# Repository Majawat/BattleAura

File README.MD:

# BattleAura

### LEDs & Sound for Warhammer

Just a fun project to add sound and lights to my Warhammer tanks. ESP32 + DFPlayer Mini + LEDs.

## What I Did

- MP3 sounds (engine, guns, etc.) from SD card
- Neopixel LEDs for glowy bits
- ESP32 does the brains, DFPlayer does the noise
- I just use buttons for triggers, but you could do more

## Parts I Used

- Seeed Studio Xaio ESP32-C3 dev board
- DFPlayer Mini
- microSD card (with MP3s)
- LEDs
- Speaker (8Ω)

## Wiring

ESP32 TX -> DFPlayer RX
ESP32 RX -> DFPlayer TX
GNDs together
5V to DFPlayer
Speaker to DFPlayer

### LED Pin assignment

- D0: Candle Fibers 1 - 3mm warm white, 3v
- D1: Candle Fibers 2 - 3mm warm white, 3v
- D2: Brazier - Chip (3.2mm) warm white, 3v
- D3: Console screen - WS2812B RGB, 5v
- D4: Weapon 1 - Nano (1.6mm) warm white, 3v
- D5: Weapon 2 - Nano (1.6mm) warm white, 3v
- D8: Engine stack 1 - Chip (3.2mm) warm white, 3v
- D9: Engine stack 2 - Chip (3.2mm) warm white, 3v
- D10: ?

### Audio files assignments
 - 0002 - Tank engine idle
 - 0003 - Weapon 1 fire
 - 0004 - Weapon 2 fire
 - 0005 - Taking hits
 - 0006 - Engine revving
 - 0007 - Destroyed
 - 0008 - Limited big weapon
 - 0009 - Killed another unit

 #### Audacity settings
  - Track > Mix > Mix stero down to Mono
  - Track > Resample > 22050 Hz
  - Effect > Normalize > -1dB
  - Export as MP3

## How I Use It

1. PlatformIO in VS Code
2. MP3s on SD card (see `audio_files/` for what I used)
3. Edit `main.cpp` for whatever effects I want
4. Upload, plug in, press buttons, enjoy

## Features that are setup

- Tank engine idle: looping sound
- Candle function

## Planned features

- Add more MP3s, add LEDs
- Add WiFi and configuration
- Try new LED patterns
- Add connection to BattleSync

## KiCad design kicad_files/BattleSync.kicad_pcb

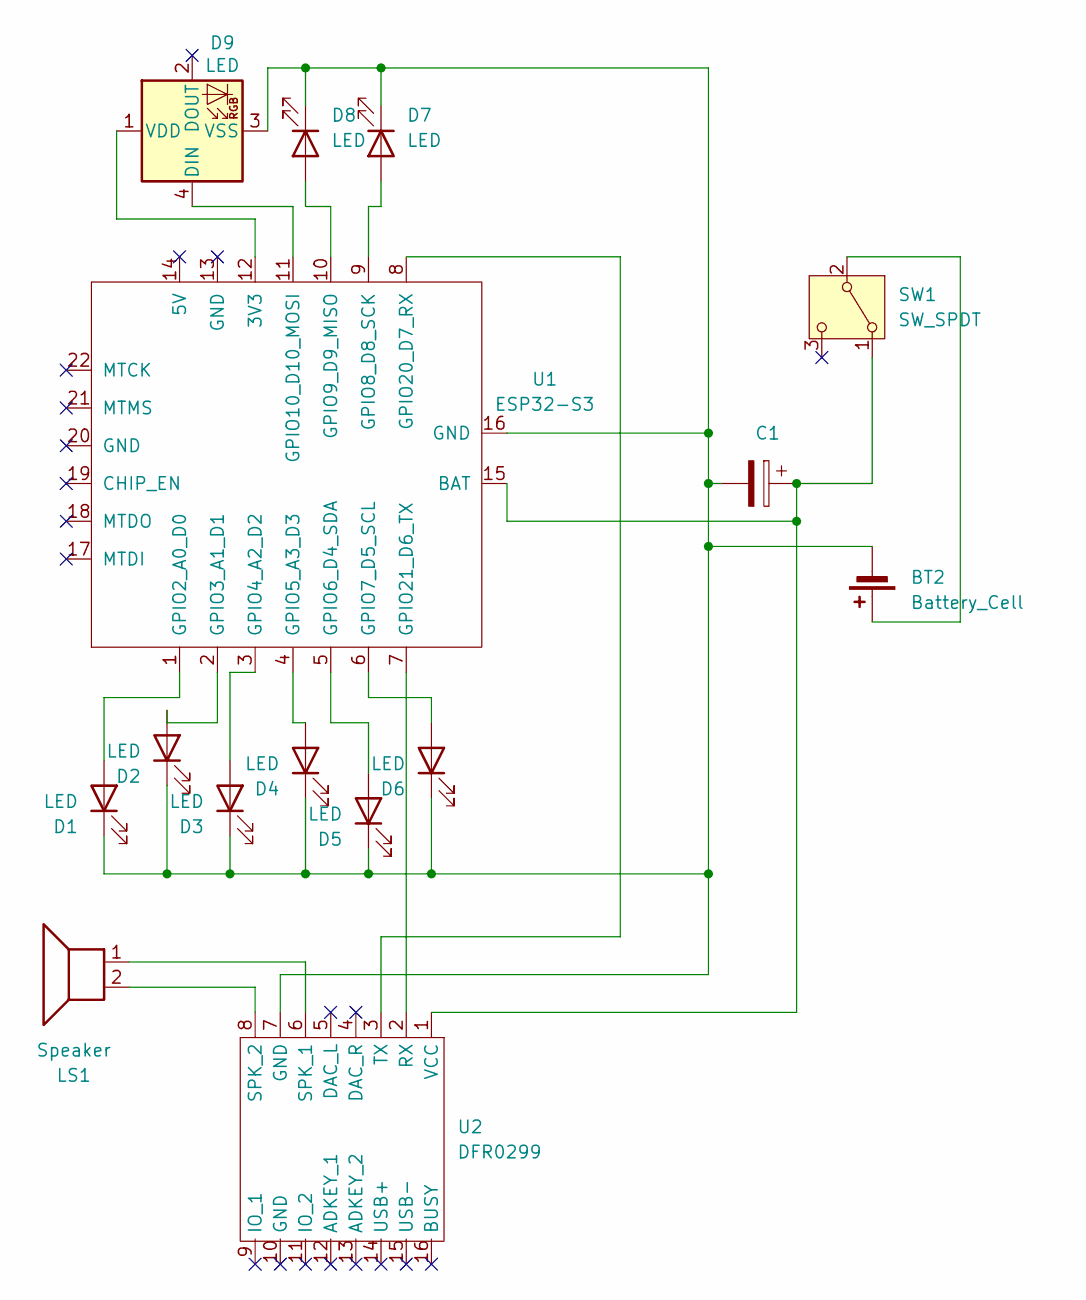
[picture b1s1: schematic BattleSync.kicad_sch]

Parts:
BT2: Battery_Cell; JST_PH_B2B-PH-K_1x02_P2.00mm_Vertical
C1: C_Polarized; CP_Radial_D4.0mm_P2.00mm
D1, D2, D3, D4, D5, D6, D7, D8: LED; SolderWire-0.1sqmm_1x02_P3.6mm_D0.4mm_OD1mm
D9: LED; SolderWire-0.1sqmm_1x03_P3.6mm_D0.4mm_OD1mm
LS1: Speaker; JST_PH_B2B-PH-K_1x02_P2.00mm_Vertical
SW1: SW_SPDT; SolderWire-0.1sqmm_1x02_P3.6mm_D0.4mm_OD1mm
U1: ESP32-S3; MCU_Seeed_ESP32C3; PARTREV 23/05/2022
U2: DFR0299; MODULE_DFR0299

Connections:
unnamed: BT2.1 (+), SW1.2 (B)
unnamed: BT2.2 (-), C1.2, D1.1 (K), D2.1 (K), D3.1 (K), D4.1 (K), D5.1 (K), D6.1 (K), D7.1 (K), D8.1 (K), D9.3 (VSS), U1.16 (GND), U2.7 (GND)
unnamed: D1.2 (A), U1.1 (GPIO2_A0_D0)
unnamed: D2.2 (A), U1.2 (GPIO3_A1_D1)
unnamed: D3.2 (A), U1.3 (GPIO4_A2_D2)
unnamed: D4.2 (A), U1.4 (GPIO5_A3_D3)
unnamed: D5.2 (A), U1.5 (GPIO6_D4_SDA)
unnamed: D6.2 (A), U1.6 (GPIO7_D5_SCL)
unnamed: D7.2 (A), U1.9 (GPIO8_D8_SCK)
unnamed: D8.2 (A), U1.10 (GPIO9_D9_MISO)
unnamed: D9.4 (VDD), U1.11 (GPIO10_D10_MOSI)
unnamed: D9.1 (DIN), U1.12 (3V3)
unnamed: C1.1, SW1.1 (A), U1.15 (MTDI), U2.1 (VCC)
unnamed: U1.8 (GPIO20_D7_RX), U2.3 (TX)
unnamed: U1.7 (GPIO21_D6_TX), U2.2 (RX)
unnamed: LS1.1, U2.6 (SPK_1)
unnamed: LS1.2, U2.8 (SPK_2)

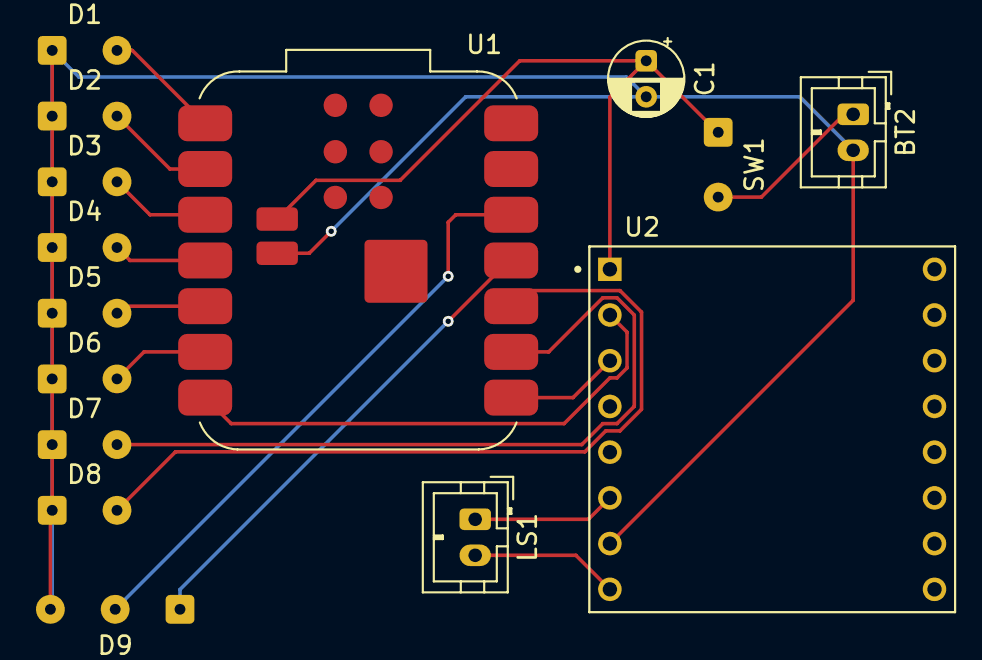
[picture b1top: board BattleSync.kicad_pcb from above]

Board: 2 copper layers, 15 parts (0 on the bottom side), 17 nets.

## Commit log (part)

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2025-08-06 Add project structure and initial implementation for DFPlayer with candle flicker effect
    - Created README files for include, lib, and test directories to provide project structure and usage instructions.
    - Added platformio.ini configuration for the Seeed Xiao ESP32C3 board with necessary library dependencies.
    - Implemented main application logic in src/main.cpp to control DFPlayer and simulate candle flicker using LEDs.
    - Included detailed error handling and status reporting for DFPlayer operations.
2025-08-06 add 2nd tank idle sound, make default
2025-08-06 Add README with project overview, wiring, and features for BattleAura
2025-08-07 Update README and main.cpp to include additional audio files and LED assignments
2025-08-07 finish adding LED options
2025-08-07 add initial sounds for most items
2025-08-11 add enginePulse effect
2025-08-11 add kicad files
2025-08-12 add two new engine effects for testing
2025-08-12 work on updating kicad files with project-level symbols and footprints
2025-08-12 remove unneeded mdns, built in.
2025-08-13 bump to 0.8.1, choose an engine effect, add version_feature line
2025-08-13 bump version number, claude build commands
2025-08-13 wifi and factory reset functions
2025-08-13 normalize files, mix down to mono
2025-08-13 record audacity settings
2025-08-13 just tiny update to test github tags
2025-08-13 minor update to trigger workflow?
2025-08-14 fix syntax error on dfplayer check
2025-08-15 correct current version string and feature
2025-08-18 Add LED types to pin assignments for reference
2025-08-23 Optimize web interface files to reduce flash usage
2025-08-23 v0.32.1: Optimize web interface to fix flash memory overflow
2025-08-23 v0.32.2: Remove WebSocket and reduce JSON usage to fit flash constraints
2025-08-23 v0.32.3: Remove HTTP client/update libraries to free 30KB+ flash space
    - Removed HTTPClient, Update, mDNS libraries
    - Minified HTML further (3.2KB -> 3.1KB)
    - Kept all core configuration and effect functionality
    - Estimated flash savings: 30-40KB
2025-08-23 v0.32.4: RESTORE OTA updates and mDNS functionality
    - Restored HTTPClient, ArduinoJson, Update, mDNS libraries
    - Added web interface update checking and OTA installation
    - Added update buttons and UI to web interface
    - Restored mDNS .local domain functionality
    - APOLOGY: I should never have removed critical update functionality without permission
2025-08-25 Fix version string to match proper dev versioning (v0.1.0-dev)
2025-08-25 Fix function declaration for handleLedControl(bool state)
2025-08-25 Fix DISABLED enum naming conflict with ESP32 framework (rename to PIN_DISABLED)
2025-08-25 Fix ledState variable references after switching to configuration-based pin management
2025-08-25 Add build commands reference - PlatformIO available at ~/.platformio/penv/bin/platformio
2025-08-25 Move build commands and critical reminders to CLAUDE.md where I will actually see them
2025-08-25 implement audio
2025-08-26 Refactor DFPlayer Mini pin configuration and restore MAX_PINS definition
2025-08-26 re-add max_pins definitions
2025-08-26 fix gpios not detected
2025-08-26 turn off leds set by pwm
2025-08-26 refresh page after led on/off
2025-08-28 start eorking on audio mapping
2025-08-28 Fix spelling: battlearua → battleaura in mDNS hostnames
2025-08-28 Add Claude development rules to prevent architectural mistakes
    - Establishes 18 core development rules in CLAUDE.md
    - Prioritizes holistic thinking over quick fixes
    - Emphasizes fixing root causes, not symptoms
    - Build & test before version increment
    - Aggressive code cleanup for pre-alpha stage
    - Preserves modular vision and priority system
2025-08-28 Reset version to 0.7.0-alpha to reflect pre-release development status
    - Changed from inflated v2.7.0 to realistic v0.7.0-alpha
    - Acknowledges we're in early development with alpha-quality software
    - Not ready for production use, still debugging core hardware functionality
    - 0.x.x format appropriate for feature-complete but unstable pre-releases
2025-08-28 v0.8.0-alpha: Add device restart functionality for WiFi configuration
    - Added /restart POST endpoint to gracefully restart the device
    - Added prominent 'Restart Device' button to config page
    - Includes user confirmation dialog and status feedback
    - Solves UX issue where WiFi changes required manual power cycling
    - Users can now: Save Config → Click Restart → Device reconnects to network
    - Flash usage: 74.8% (minimal increase)
2025-08-31 Fix critical frontend resource paths - CSS and status route
    - Fixed /style.css route (was incorrectly /styles.css)
    - Added missing /status route pointing to system.html
    - Frontend will now load CSS and navigation will work
    These were critical 404 errors preventing the UI from working at all.
2025-08-31 Add missing config page routes
    - /config/device -> device.html
    - /config/pins -> pins.html
    - /config/effects -> effects.html
    - /config/system -> system.html
    These routes were referenced by the frontend but missing from backend.
2025-08-31 Bump version to 0.11.1-alpha and set WiFi hostname before connection
2025-08-31 start fixing all the bullshit fuckin' claude broke again.
2025-09-03 revert webinterface changes to fix heap fragmentation issue
2025-09-04 Recreate readme with my setup notes
2025-10-21 feat: Update PlatformIO library dependencies
2025-10-21 docs: Update GEMINI.md to reflect current project state
